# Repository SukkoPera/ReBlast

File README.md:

# ReBlast

ReBlast is an 8-bit Digital-to-Analog + Analog-to-Digital converter add-on for Commodore 16, 116 and Plus/4 SIDcards.

## Summary
ReBlast is basically a replica of [Solder of Synergy's Digi-Blaster](https://plus4world.powweb.com/hardware/Digi-Blaster). It uses the [ZN428](doc/zn428.pdf) DAC originally made by Ferranti and the [ADC0804](doc/adc0804.pdf) ADC by Signetics. Both these chips are old-fashioned and out of production, but they can still be found relatively easily and cheaply.

ReBlast was sized and shaped so that it fits perfectly on a [ReSeed](https://github.com/SukkoPera/ReSeed) card.

The DAC feeds its output into the SID's EXT_IN pin, which means that you will hear it mixed with the computer audio or on the output jack of the ReSeed card. Similarly, the ADC takes its input from the ReSeed input jack.

The DAC part of ReBlast is compatible with [ReVox](https://github.com/SukkoPera/ReVox), but ReBlast can also take advantage of the SID to apply filters to the audio signal.

APOS's [Digital Composing Kit 2.0](https://plus4world.powweb.com/software/Digital_Composing_Kit_V2_0) or [the older version](https://plus4world.powweb.com/software/Digital_Composing_Kit) can be used to sample, compose and edit samples.

## Installation
### ReSeed
Installation is very easy, in particular if your ReSeed card was build with the DC-DC step-up converter and no regulator at U6:
- Remove the SID chip from your board.
- Plug ReBlast where the SID chip was.
- Plug the SID into the socket on the ReBlast board.

If your ReSeed was built with the TL497 and/or with a linear regulator at U6, you will probably need to use a few chip sockets as "spacers" in order for the board to rise enough over the other components. If you really want to use a linear regulator, it is probably best to use an L78L09/L78L12 since they are much less tall than the LM7809/LM7812.

When plugging ReSeed into your computer, it might feel like ReBlast is preventing it from being completely inserted, but the card should actually slide in enough to work correctly.

### LittleSixteen
ReBlast has not yet been tested on a LittleSixteen board, but there is no reason why it should not work, except for physical fitting issues. Probably the usage of additional spacer sockets is necessary, as well as using smaller voltage regulators.

## Testing
I suggest to use [WavePlay-SD](https://plus4world.powweb.com/software/WavePlay-SD), a great piece of software that plays music with superb quality. Enter the Setup menu with <kbd>CTRL+S</kbd> and select *INT. INTL DGB:0* using the *MOD* button.

More software for the card can be found [here](https://plus4world.powweb.com/effects/Digi-Blaster_Support).

## Programming
### DAC
The DAC is exposed at address $FD5E or $FE9E.

ReVox has no buffer, which means it must be fed audio samples in real-time. This is not a trivial task and existing software should be analyzed in order to learn the best techniques to do so.

Keep in mind that since the DAC feeds its output into the SID's EXT_IN pin, so the volume for that must be set through $FD58. This also opens interesting possibilities since the SID can apply filters to the audio coming in through that pin. See [Second Mod](https://plus4world.powweb.com/software/Second_Mod) for an example of that.

Detailed information, including code, can be found on the [ReVox Wiki](https://github.com/SukkoPera/ReVox/wiki).

### ADC
The ADC is exposed at $FD5F or $FE9F (64863 decimal). First of all, it needs calibration. This can easily be done with the following BASIC line:

    DO : POKE 64863,0 : PRINT PEEK(64863) : LOOP

Then use a screwdriver to turn the pot on the board until the displayed value is mostly stable around 128.

Writing any value to the register starts the sampling process. Then at least 48 clock cycles must elapse before the sampled value can be read from the same register. Since the conversion is directly linked to the clock of the Plus/4, this means that the smallest timer value for timer 1 is 48.

## Releases
If you want to get this board produced, you are recommended to get [the latest release](https://github.com/SukkoPera/ReBlast/releases) rather than the current git version, as the latter might be under development and is not guaranteed to be working.

Every release is accompanied by its Bill Of Materials (BOM) file and any relevant notes about it, which you are recommended to read carefully.

## License
The ReBlast documentation, including the design itself, is copyright &copy; SukkoPera 2024 and is licensed under the [Creative Commons Attribution-NonCommercial-ShareAlike 4.0 International License](https://creativecommons.org/licenses/by-nc-sa/4.0/).

This documentation is distributed *as is* and WITHOUT ANY EXPRESS OR IMPLIED WARRANTIES whatsoever with respect to its functionality, operability or use, including, without limitation, any implied warranties OF MERCHANTABILITY, SATISFACTORY QUALITY, FITNESS FOR A PARTICULAR PURPOSE or infringement. We expressly disclaim any liability whatsoever for any direct, indirect, consequential, incidental or special damages, including, without limitation, lost revenues, lost profits, losses resulting from business interruption or loss of data, regardless of the form of action or legal theory under which the liability may be asserted, even if advised of the possibility or likelihood of such damages.

## Support the Project
If you want to get some boards manufactured, you can get them from PCBWay through this link:

You get my gratitude and cheap, professionally-made and good quality PCBs, I get some credit that will help with this and [other projects](https://www.pcbway.com/project/member/shareproject/?bmbid=41100). You won't even have to worry about the various PCB options, it's all pre-configured for you!

Also, if you still have to register, [you can use this link](https://www.pcbway.com/setinvite.aspx?inviteid=41100) to get some bonus initial credit (and yield me some more).

You can also buy me a coffee if you want:

## Thanks
- Solder, for designing the original card and sharing its schematics.
- Haegar and TLC, for help with the design.
- Lettercorner Studio for the [Sterion Font](https://www.fontspace.com/sterion-font-f113971) used in the logo.

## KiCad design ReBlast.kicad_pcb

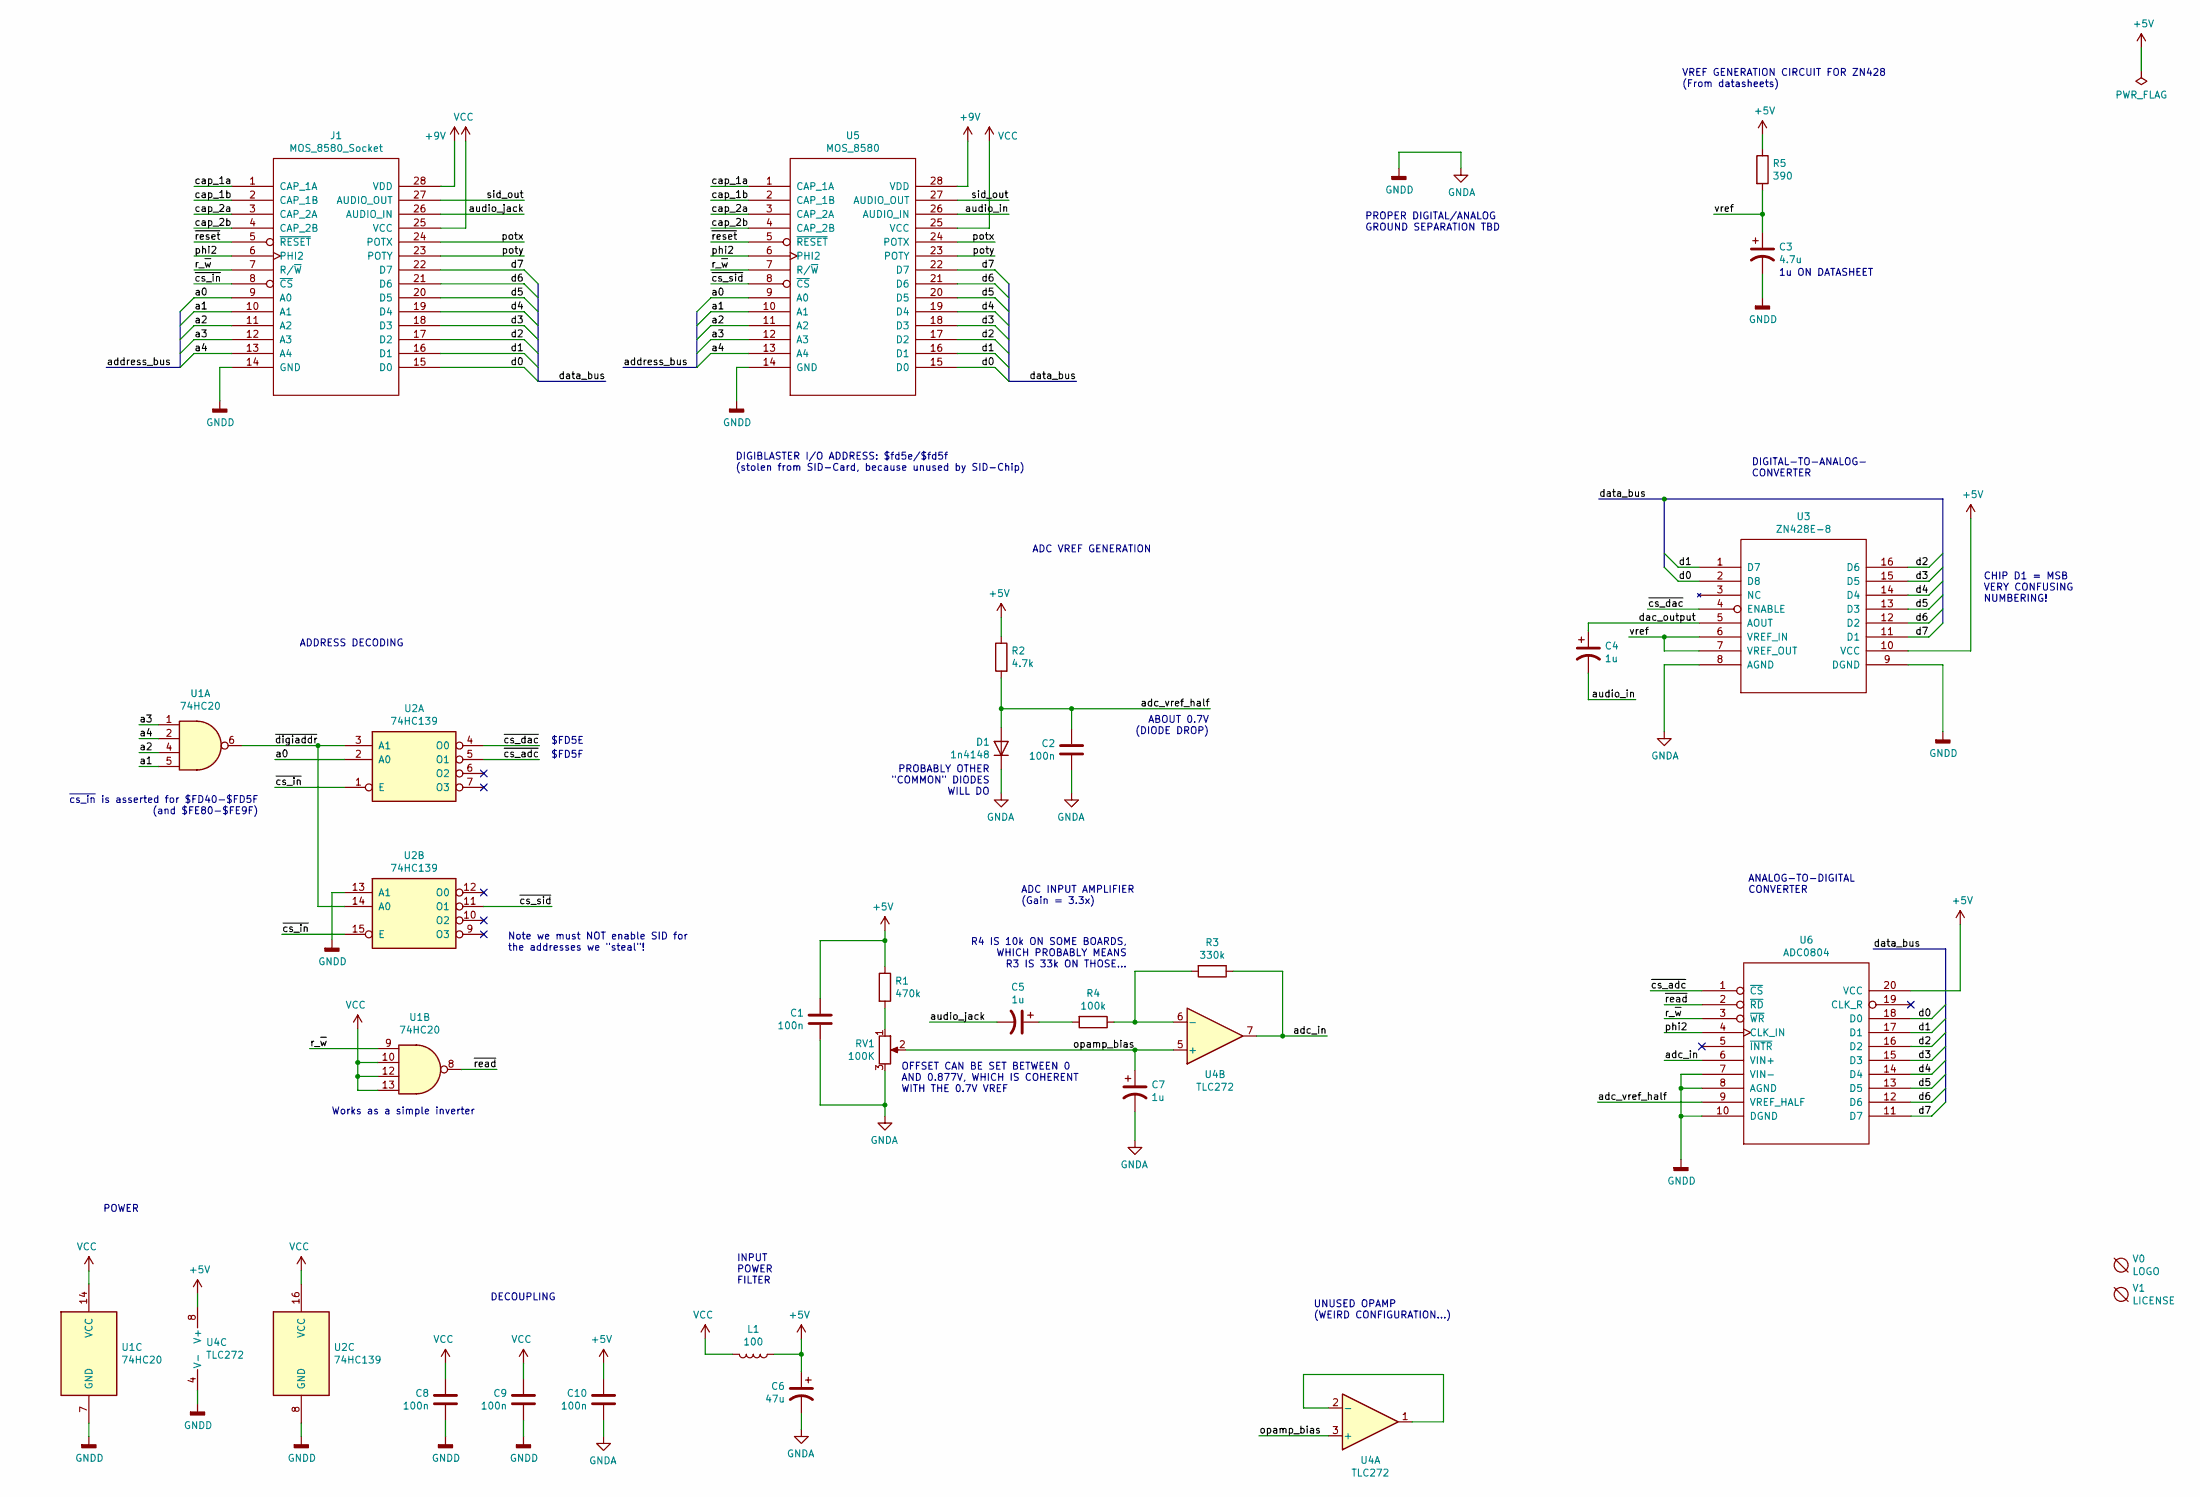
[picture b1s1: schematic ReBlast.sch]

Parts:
C1, C2, C8, C9, C10: 100n; C_Disc_D7.0mm_W2.5mm_P5.00mm
C3: 4.7u; CP_Radial_D5.0mm_P2.00mm
C4, C5, C7: 1u; CP_Radial_D5.0mm_P2.00mm
C6: 47u; CP_Radial_D6.3mm_P2.50mm
D1: 1n4148; D_DO-35_SOD27_P2.54mm_Vertical_KathodeUp
J1: MOS_8580_Socket; DIP-28_W15.24mm_Socket
L1: 100; L_Radial_D6.0mm_P4.00mm
R1: 470k; R_Axial_DIN0207_L6.3mm_D2.5mm_P2.54mm_Vertical
R2: 4.7k; R_Axial_DIN0207_L6.3mm_D2.5mm_P2.54mm_Vertical
R3: 330k; R_Axial_DIN0207_L6.3mm_D2.5mm_P2.54mm_Vertical
R4: 100k; R_Axial_DIN0207_L6.3mm_D2.5mm_P2.54mm_Vertical
R5: 390; R_Axial_DIN0207_L6.3mm_D2.5mm_P2.54mm_Vertical
RV1: 100K; Pot_Bourns_3306P
U1: 74HC20; DIP-14_W7.62mm_Socket_LongPads
U2: 74HC139; DIP-16_W7.62mm_Socket_LongPads
U3: ZN428E-8; DIP-16_W7.62mm_Socket
U4: TLC272; DIP-8_W7.62mm_Socket
U5: MOS_8580; DIP-28_W15.24mm_Socket
U6: ADC0804; DIP-20_W7.62mm_Socket
V0: LOGO; logo
V1: LICENSE; cc_by_nc_sa_small

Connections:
+5V: C1.1, C6.1, C10.1, L1.2, R1.1, R2.1, R5.1, U3.10 (VCC), U4.8 (V+), U6.20 (VCC)
+9V: J1.28 (VDD), U5.28 (VDD)
/a0: J1.9 (A0), U2.2 (A0), U5.9 (A0)
/a1: J1.10 (A1), U1.5, U5.10 (A1)
/a2: J1.11 (A2), U1.4, U5.11 (A2)
/a3: J1.12 (A3), U1.1, U5.12 (A3)
/a4: J1.13 (A4), U1.2, U5.13 (A4)
/adc_in: R3.1, U4.7, U6.6 (VIN+)
/adc_vref_half: C2.1, D1.2 (A), R2.2, U6.9 (VREF_HALF)
/audio_in: C4.2, U5.26 (AUDIO_IN)
/audio_jack: C5.2, J1.26 (AUDIO_IN)
/cap_1a: J1.1 (CAP_1A), U5.1 (CAP_1A)
/cap_1b: J1.2 (CAP_1B), U5.2 (CAP_1B)
/cap_2a: J1.3 (CAP_2A), U5.3 (CAP_2A)
/cap_2b: J1.4 (CAP_2B), U5.4 (CAP_2B)
/d0: J1.15 (D0), U3.2 (D8), U5.15 (D0), U6.18 (D0)
/d1: J1.16 (D1), U3.1 (D7), U5.16 (D1), U6.17 (D1)
/d2: J1.17 (D2), U3.16 (D6), U5.17 (D2), U6.16 (D2)
/d3: J1.18 (D3), U3.15 (D5), U5.18 (D3), U6.15 (D3)
/d4: J1.19 (D4), U3.14 (D4), U5.19 (D4), U6.14 (D4)
/d5: J1.20 (D5), U3.13 (D3), U5.20 (D5), U6.13 (D5)
/d6: J1.21 (D6), U3.12 (D2), U5.21 (D6), U6.12 (D6)
/d7: J1.22 (D7), U3.11 (D1), U5.22 (D7), U6.11 (D7)
/dac_output: C4.1, U3.5 (AOUT)
/opamp_bias: C7.1, RV1.2, U4.3 (+), U4.5 (+)
/phi2: J1.6 (PHI2), U5.6 (PHI2), U6.4 (CLK_IN)
/potx: J1.24 (POTX), U5.24 (POTX)
/poty: J1.23 (POTY), U5.23 (POTY)
/r_~w: J1.7 (R/~W), U1.9, U5.7 (R/~W), U6.3 (~WR)
/sid_out: J1.27 (AUDIO_OUT), U5.27 (AUDIO_OUT)
/vref: C3.1, R5.2, U3.6 (VREF_IN), U3.7 (VREF_OUT)
/~cs_adc: U2.5 (O1), U6.1 (~CS)
/~cs_dac: U2.4 (O0), U3.4 (ENABLE)
/~cs_in: J1.8 (~CS), U2.1 (E), U2.15 (E)
/~cs_sid: U2.11 (O1), U5.8 (~CS)
/~digiaddr: U1.6, U2.3 (A1), U2.14 (A0)
/~read: U1.8, U6.2 (~RD)
/~reset: J1.5 (~RESET), U5.5 (~RESET)
GNDA: C1.2, C2.2, C3.2, C6.2, C7.2, C8.2, C9.2, C10.2, D1.1 (K), J1.14 (GND), RV1.3, U1.7 (GND), U2.8 (GND), U2.13 (A1), U3.8 (AGND), U3.9 (DGND), U4.4 (V-), U5.14 (GND), U6.7 (VIN-), U6.8 (AGND), U6.10 (DGND)
unnamed: C5.1, R4.2
unnamed: R1.2, RV1.1
unnamed: R3.2, R4.1, U4.6 (-)
unnamed: U4.1, U4.2 (-)
VCC: C8.1, C9.1, J1.25 (VCC), L1.1, U1.10, U1.12, U1.13, U1.14 (VCC), U2.16 (VCC), U5.25 (VCC)

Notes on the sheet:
DIGIBLASTER I/O ADDRESS: $fd5e/$fd5f (stolen from SID-Card, because unused by SID-Chip)
$FD5E
$FD5F
VREF GENERATION CIRCUIT FOR ZN428 (From datasheets)
ANALOG-TO-DIGITAL CONVERTER
DIGITAL-TO-ANALOG- CONVERTER
ADDRESS DECODING
Note we must NOT enable SID for the addresses we "steal"!
CHIP D1 = MSB VERY CONFUSING NUMBERING!
INPUT POWER FILTER
1u ON DATASHEET
PROPER DIGITAL/ANALOG GROUND SEPARATION TBD
R4 IS 10k ON SOME BOARDS, WHICH PROBABLY MEANS R3 IS 33k ON THOSE...
PROBABLY OTHER "COMMON" DIODES WILL DO
UNUSED OPAMP (WEIRD CONFIGURATION...)
~cs_in~ is asserted for $FD40-$FD5F (and $FE80-$FE9F)
Works as a simple inverter
ADC INPUT AMPLIFIER (Gain = 3.3x)
ADC VREF GENERATION
OFFSET CAN BE SET BETWEEN 0 AND 0.877V, WHICH IS COHERENT WITH THE 0.7V VREF
ABOUT 0.7V (DIODE DROP)
DECOUPLING
POWER

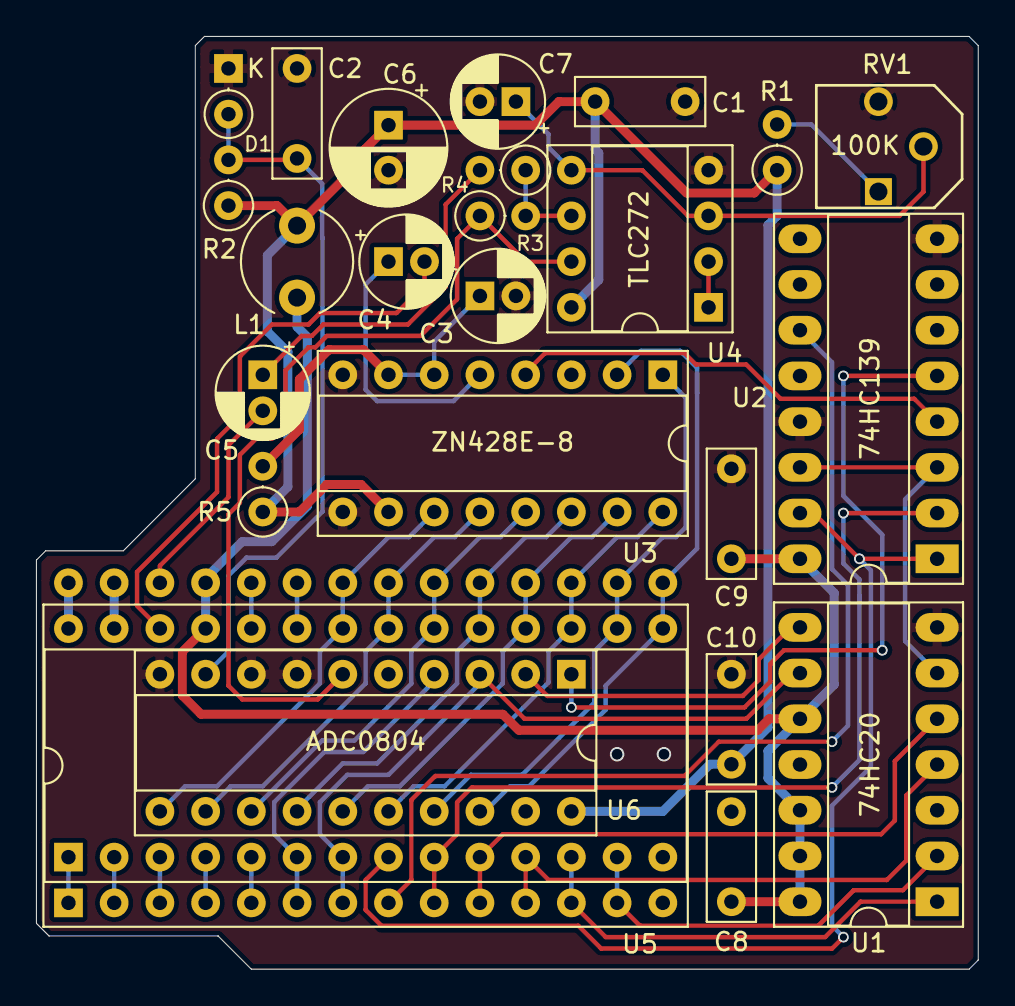
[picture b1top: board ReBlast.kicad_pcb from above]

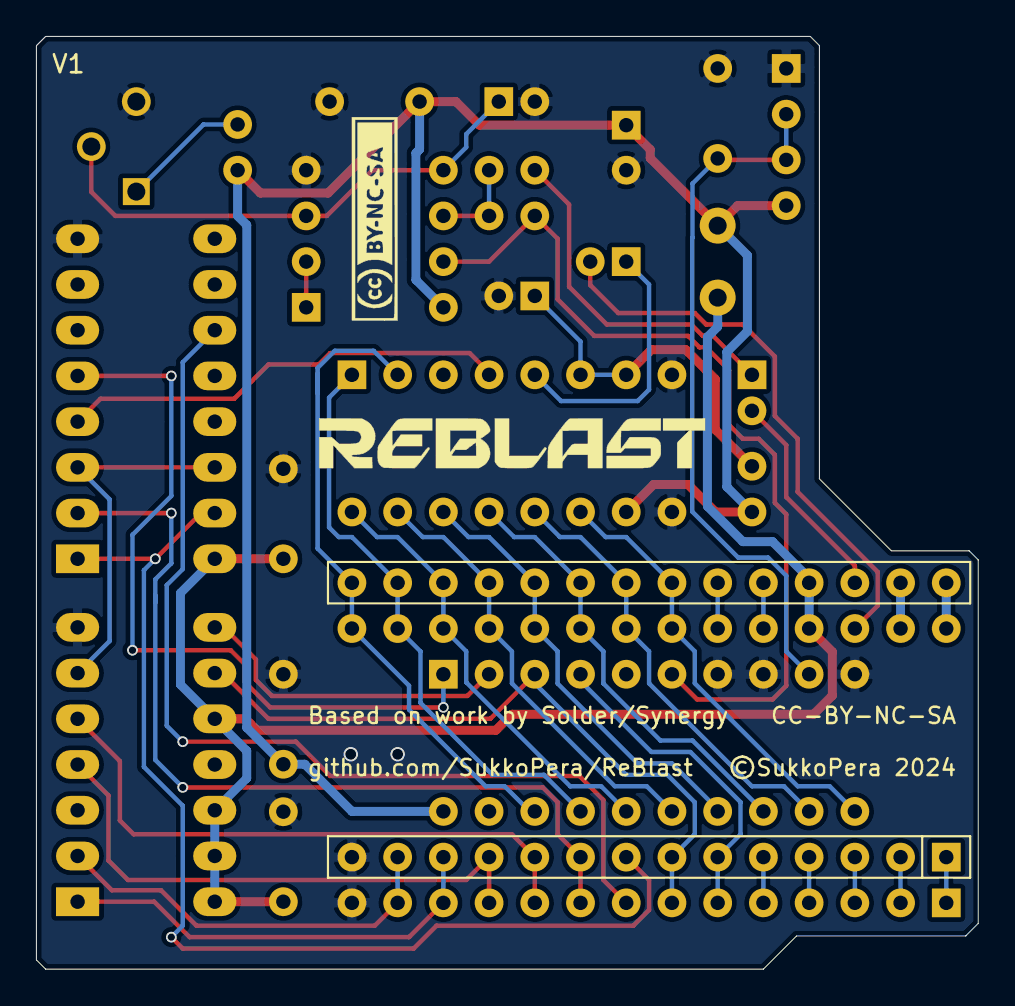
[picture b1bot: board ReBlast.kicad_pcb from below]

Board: 2 copper layers, 52.3 x 51.8 mm, 27 parts (2 on the bottom side), 44 nets.

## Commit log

2026-03-06 Power circuit almost makes sense
2026-03-06 AT LAAAAAAAAAST! Though I must admit that R6 is really misleading...
2026-03-06 Add some notes, fix ERC, adjust some tracks
2026-03-06 Done?
2026-03-06 Better ground plane
2026-03-06 Back side is 99% done. Top side is full of doubts...
2026-03-06 Try to come up with some values for caps
2026-03-06 Fix socket
2026-03-06 Nothing makes sense
2026-03-06 Checkpoint!
2026-03-06 Fix DRC
2026-03-06 Almost there...
2026-03-06 Suppositions in progress...
2026-03-06 Center U6 within U5
2026-03-06 Swap SID socket and connector This is so that the board sits a bit further up the ReBlast card and doesn't hit the computer case
2026-03-06 Add logo, etc.
2026-03-06 Update renders

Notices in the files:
ReBlast.kicad_pcb:
Licensed under CC BY-NC-SA 4.0
